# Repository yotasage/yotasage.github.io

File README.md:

# yotasage.github.io

My own collection of tools, so I don't have to search other people's websites for one that is good enough, without
ads and bad design.

**Site:** https://yotasage.github.io/

Every tool runs entirely in the browser. There is no server: the site is a static export hosted on GitHub Pages, and
files given to a tool never leave the device.

| | |
| :-: | :-: |
| <br>[**PCB viewer**](https://yotasage.github.io/pcb-viewer/main) — Gerber, KiCad, Altium, PADS & EAGLE | <br>[**EM simulation**](https://yotasage.github.io/em-sim/main) — 2D trace solver, 3D vias & WebGPU FDTD |
| <br>[**Smith chart**](https://yotasage.github.io/smith-chart/main) — Interactive matching, solver & TikZ export | <br>[**Resistor lookup**](https://yotasage.github.io/resistor/main) — E-series, SMD/colour codes, combinations & design |
| <br>[**3D viewer**](https://yotasage.github.io/3d-viewer/main) — STEP, IGES, BREP & mesh formats | <br>[**PDF tools**](https://yotasage.github.io/pdf/main) — 33 private client-side PDF utilities |

## Tools

Every tool has a card on the main page ([pages/index.tsx](pages/index.tsx)).

| Tool | Page | What it does |
| --- | --- | --- |
| FFT & coherent sampling | [/simsetup/main](https://yotasage.github.io/simsetup/main) | Calculates sampling parameters for FFTs and simulations (f0, FS, Ncyc, Npts and what follows from them), with checks for coherent sampling. |
| QR code generator | [/qrcode/main](https://yotasage.github.io/qrcode/main) | QR Code Model 1 and 2, Micro QR and rMQR with control over every parameter. Exports PNG, JPG, SVG and PDF. |
| QR code reader | [/qr-reader/main](https://yotasage.github.io/qr-reader/main) | Reads QR Code, Micro QR and rMQR (and, when asked, Data Matrix, Aztec, PDF417, EAN, UPC, Code 128 and other barcodes) from the camera (pausing at the first code or adding each new one; camera choice, light and zoom where the phone has them), from images, screenshots and every page of a PDF (chosen, dropped or pasted), several codes per picture, also inverted, mirrored or turned, with each code outlined and numbered; a code that is found but too damaged is outlined and said so. Shows what a code holds: Wi-Fi networks (password hidden until shown), eSIM activation codes (SM-DP+ address and activation code to copy, and Apple's install link on an iPhone), links with warnings for look-alike addresses, user names before "@", plain http and link shorteners, contacts (vCard, MeCard, BIZCARD; saved as .vcf), calendar events (.ics), email, SMS, phone numbers, locations with map links, two-factor accounts with their live codes (otpauth and Google Authenticator's export), SEPA (EPC) and Swiss QR bill payments with IBAN and reference checks, crypto payment links, GS1 product data and Digital Links, Matter setup codes with the manual pairing code, boarding passes (IATA BCBP), Wi-Fi Easy Connect, JSON, data URLs, the generator's password-protected text (decrypted with the password), and images, ZIP, gzip or zlib data stored as bytes. Joins structured-append messages from any pictures. A raw view gives the text with control and invisible characters named, a hex dump and the bytes read in another character set; a symbol view redraws the modules with version, error correction, mask and the symbology identifier. Typed or pasted text is shown the same way. |
| PDF tools | [/pdf/main](https://yotasage.github.io/pdf/main) | 33 client-side PDF tools: reading, visual and text comparison, merging, splitting, organizing, rotating, removing and extracting pages, compressing, web optimization (linearizing), repairing, self-hosted OCR, editing, signing, filling forms, page numbers, watermarks, cropping, resizing, N-up, grayscale, dark mode/invert, redacting, protecting, unlocking, converting to/from images and PDF/A, flattening, and editing or removing metadata, with in-memory handoff between tools. Plan: [docs/pdf-tools-plan.md](docs/pdf-tools-plan.md). |
| Base64 image converter | [/base64-image/main](https://yotasage.github.io/base64-image/main) | Image to Base64, a data URL or an HTML, CSS or Markdown snippet (optionally converted to PNG, JPEG or WebP first), and Base64 back to an image to view, download or copy. |
| Text case converter | [/text-case/main](https://yotasage.github.io/text-case/main) | Sentence case, lower case, UPPER CASE, Capitalized Case, Title Case (Chicago or APA), alternating and inverse case, and names for code (camelCase, PascalCase, snake_case, CONSTANT_CASE, kebab-case, Train-Case, dot.case), with character, word and line counts. |
| 3D viewer | [/3d-viewer/main](https://yotasage.github.io/3d-viewer/main) | Views STEP, IGES and BREP (with Open CASCADE), STL, 3MF, AMF, OBJ, PLY, OFF, VTK, glTF/GLB, FBX, Collada, KMZ, 3DS, USD/USDZ, VRML, XYZ, PCD, G-code and MagicaVoxel files. Several files can be opened together and moved apart to compare them. Section view, distance measuring, size, surface area and volume, a parts tree, and saving as STL, OBJ, PLY, GLB or PNG. |
| PCB viewer | [/pcb-viewer/main](https://yotasage.github.io/pcb-viewer/main) | Views the Gerber and drill files of a circuit board (Gerber RS-274X and X2, also the old commands of older files; Excellon with slots and routed holes, also without a header, whose format is then found from the pads; Gerber drill files) or a KiCad board (.kicad_pcb of KiCad 4 to 10, and footprints, .kicad_mod), an Altium board (.PcbDoc, binary and ASCII, and binary footprint libraries, .PcbLib), a PADS ASCII board (.asc of PowerPCB V4.0 to current PADS Layout; a binary .pcb is to be exported as ASCII in PADS) or an EAGLE board (.brd of EAGLE 6 to 9 and the EAGLE files Fusion 360 exports, and libraries, .lbr; a binary .brd from before EAGLE 6 is to be saved as XML), opened as files, a folder or ZIP archives. A pick-and-place file opened with Gerber files (KiCad's CSV and .pos, Altium's, JLCPCB's, EAGLE's .mnt and .mnb, Fusion 360's, or any table whose columns are chosen by hand; recognised by content) marks each part on the board with its rotation and designator, top and bottom, and lists the parts; its units, origin and negated bottom X are fitted to the pads when the file does not say, and can be changed. A KiCad board is drawn as KiCad plots it: pads of every shape with their solder mask and paste openings, tracks, vias, zones as last filled, graphics, text in KiCad's stroke font (or the outlines the file stores for TrueType text) and holes; from a project folder the board file is chosen and copies in backups are left out. An Altium board is drawn with its layer stack and mechanical layers, pad stacks, solder mask and paste openings from the pads and the design rules, vias, tracks, fills, regions, polygons as last poured, internal planes (with clearances and thermal reliefs), board cutouts, and text in the stroke font in the place and size of Altium's own. A PADS board is drawn with its layers from the file's layer data, part decals (outlines, copper of pins, labels), pad stacks (round, square, rounded, annular, oval and rectangular fingers with offsets, drills, slots, plating, solder mask and paste entries), routes with arcs, vias and teardrops, copper pours as last flooded, 2D lines, keep-outs and copper cut-outs, the board outline with its cutouts, and text in the stroke font in the place and size of PADS's own; plane areas whose flood the file does not keep are drawn from their outlines, clear of other nets by the design rules, and CAM planes as negative planes with antipads and thermal reliefs. An EAGLE board is drawn with its layer setup and layers, the packages of its elements placed and mirrored for the bottom, pads and vias sized by the design rules (restring, octagon, long and offset pads, SMD roundness, solder stop and cream masks), wires with arcs, holes, plain items, smashed attribute texts, and text in the stroke font in the place and size of EAGLE's vector font; EAGLE stores no copper for its polygons, so they are drawn from their outlines, clear of other signals by their isolation and the design rules, by rank, without thermal reliefs or the removal of islands. The layers are identified from their X2 attributes, the Gerber job file or their file names (KiCad, Altium, EAGLE, OrCAD, DipTrace, EasyEDA, PADS), and each can be shown, hidden, recoloured, made transparent, reordered or given another type. A realistic view shows the top or the bottom as the board looks (board shape with cutouts, solder mask, finish, silkscreen and holes; colours from the job file, the KiCad stackup or chosen). Pan, zoom and pinch, coordinates in mm or inch, measuring in mm and mil that snaps to pads, holes and line ends, the board size, stackup, components and nets, and saving the view as PNG (on screen or the whole board at a chosen resolution, transparent if wanted) or SVG (vectors at 1:1). The shown layers can be saved as a PDF at exactly 1:1 (all on one page or one page per layer; A4, A3, Letter or a page fitted to the board; seen from the top, the bottom or each layer from its own side; in the layer colours, as on screen or black; with a title, a scale bar and the layers as PDF layers) and as DXF (in mm, each layer on a layer of its own), or the board outline and its holes as DXF for mechanical CAD; layers with clear areas (negative planes, EAGLE polygons, Gerber clear polarity) are flattened with polygon booleans, so both stay vectors. A click or tap says what is there (pad, track, via, zone, hole or component, with its net, component, pin, size, layers and drill; for Gerber files from their X2 attributes, else layer, aperture and size), and clicking again steps through what overlaps there. A net or a component can be highlighted on every layer, also in the realistic view and the saved images, from a click or from searchable lists of components and nets that zoom to it. A KiCad, Altium, PADS or EAGLE board's BOM and pick-and-place file can be saved as CSV, as KiCad writes position files, from the file's origin, the drill/place (KiCad) or board (Altium) origin or the board's corner. An Altium, PADS or EAGLE board can be saved as a KiCad board (.kicad_pcb in KiCad 9's format, which KiCad 9 and 10 open), after a warning that the conversion may be incomplete or wrong and must be checked in KiCad: the layers with their names (mechanical and other layers as user layers), nets, a footprint per component with its pads (every shape, pad stacks, holes and slots, solder mask and paste margins), graphics, texts, reference and value, tracks, arcs and vias (blind, buried and micro too), zones with their saved fill, keep-outs and cut-outs as rule areas, and the board outline; planes whose copper the file does not keep (internal and CAM planes, PADS plane areas, EAGLE polygons) are zones filled with the copper drawn here. Other files are listed with what they are. Plan: [docs/pcb-viewer/plan.md](docs/pcb-viewer/plan.md). |
| Smith chart | [/smith-chart/main](https://yotasage.github.io/smith-chart/main) | Builds a matching circuit from the load to the source out of series and shunt R, L and C, transmission lines, open and short stubs and λ/4 transformers (up to 24 parts; Z0, f0 and the load typed, ideal parts and lossless lines), and draws its path on a Smith chart: every part's exact arc in its colour with an arrow in the direction of travel, a marker at every node and the match with a VSWR 1.5 circle. The grid shows impedance, admittance or both and zooms and pans by mouse, keys and touch, with labels that follow the zoom; a readout gives z, y, Γ, VSWR and return loss under the pointer. Parts are added, removed and reordered by mouse or keys, their values typed in any of their forms (R, L or C, the reactance or susceptance at f0, the normalised value, a line's length in λ or degrees and its Zc), dragged by a handle on the chart (snapping to the grid circles and to standard values: E6–E96, an own pasted list or any value per kind; Alt or the Snap switch off), stepped by arrow keys, or drawn out of the input with the draw tool; a node table gives z, Γ, VSWR and return loss of every node. Finds missing values: mark one or two values (or f0, or a line's Zc) as unknown and pick a goal at any node (the centre, a point Z, a VSWR, |Γ| or return-loss circle or limit, an r, g, x or b circle), and it lists every solution with |Γ|, the construction's two circles on the chart, a preview path and Apply, the nearest standard values and what they cost in match, the ranges that keep an inequality goal, families of two unknowns with a slider, and plainly why there is none; with nothing marked it suggests the smallest change of one or two values that meets the goal. A frequency sweep draws Γ(f) on the chart with markers, a return-loss or VSWR plot and the band figures, and a report prints it all. Exports, made on the device: the chart as a figure for a report (a TikZ picture or standalone document, SVG, PNG at 1× to 8×; column, text or page width or any width, detail presets or each item on its own, colour, greyscale or black and white, previewed at true size), CSV of the nodes, the trace and the markers, Touchstone `.s1p` of S11 over the sweep, and the project file (circuit, goal, sweep, value lists and export settings; opened again by a file picker or a drop on the page), and Copy link. An Equations panel shows the equations of any part, node or readout with your numbers, coloured and linked both ways to the chart, with step-by-step derivations, and "Explain this move" says in words what a part does to the path. A Theory section explains the chart, the solver and the sweep with live numbers, equations and citations, and every control has a short line linking to it. Learn: 16 worked examples with a guide that checks each step, exercises of five kinds with a hint ladder, and lesson links that lock parts of the page for a student. Undo and redo (200 steps), Start over, light and dark themes, every task by keyboard alone and by touch, checked in Edge, Firefox and WebKit, and the whole circuit is in the link. How to use it: [docs/smith-chart/howto.md](docs/smith-chart/howto.md); plan: [docs/smith-chart/plan.md](docs/smith-chart/plan.md). |
| Resistor lookup | [/resistor/main](https://yotasage.github.io/resistor/main) | Reads a resistance in any notation (4k7, 4,7 kΩ, 4700, 10m), the marking of a chip resistor (three or four characters, EIA-96, milliohm forms, also upside down) or the colours of 3 to 6 bands from either end, shows every reading when a text has several (digits alone are a value first, or a marking first when "Read as" says so; a reading from the other end is marked more likely or unlikely), and gives the value below, above and nearest in E3 to E192 with signed errors, the colour bands and the SMD markings. Draws the part as an axial resistor with 3 to 6 bands (four body sizes and colours) or as a chip resistor of any size from 01005 to 2512 with its marking (3 digits, 4 digits or EIA-96), in a realistic and a flat style: click a band to choose its colour, read the part from the other end, or type the marking, and the value follows. Saves the drawing as SVG, PNG, JPG or WebP at a chosen width and background, with a caption and scale bar or as the part alone, or copies it; the flat drawing is also saved or copied as TikZ for LaTeX (a `.tex` file that compiles as it is). Combinations finds the networks of 1 to 4 real resistors (series, parallel or both) that come closest to the value, from an E-series over a range or from your own value lists (pasted in any notation, kept in the browser, carried by the link): a small circuit drawing, the formula, the signed error, worst-case and RSS tolerance for each, the share of voltage, current and power in every resistor, watts and the smallest chip size for a voltage or a current, copy as text and save as CSV. Design finds the resistors for a circuit and checks them over tolerance and temperature: a single resistance for a current or a voltage (with a series drop for an LED), a voltage divider with an optional load, the feedback of a regulator, a non-inverting or inverting gain, and a current-sense shunt, each with a schematic; for a target, an allowed deviation, a kind of part (tolerance and TCR), a set of temperatures (−40, 25, 85 and 125 °C unless changed) and parts that drift on their own or track, it answers in one sentence which values stay inside, or which tolerance and TCR would be needed, and lists the candidates (also two values in series or parallel) with the worst case and RSS at each temperature in a range chart, and the voltage, current and power in each resistor against the derated rating of a chip size. Reference tables (colour code, SMD markings, EIA-96, chip and axial sizes with limiting voltages) mark the current value and use what is clicked; where makers disagree the page says so (an EIA-96 marking with R or S is read both ways). Theory explains what stands behind the numbers in fourteen short topics that fold (Ohm's law and power, series, parallel and dividers, the E-series, reading the codes, technologies compared, tolerance and temperature with worst case and RSS, power, derating and limiting voltage, pulses, noise, voltage coefficient, high frequency, ageing, zero-ohm links, current sensing), with formulas, small figures and live numbers for the current value (current and power at a typed voltage, thermal noise, the derating curve of the chosen chip size, the series the value is in). Every sourced statement is cited, and References lists the sources (datasheets, application notes, the standards and the original papers) from `references.bib`, numbered by first citation. Light and dark themes, and every result is a link. How it was built is in [docs/resistor/plan.md](docs/resistor/plan.md). |
| EM simulation | [/em-sim/main](https://yotasage.github.io/em-sim/main) | Works out the impedance of PCB traces and vias with field solvers, on a stackup you type, any of JLCPCB's stackups or the stackup and net classes of a KiCad board. Traces (a 2D field solver): Z0, Zdiff, Zcm, Zodd, Zeven, εeff, delay, crosstalk, L and C, each with the solver's error, for microstrip, stripline, coplanar lines with or without ground, edge- and broadside-coupled pairs or any arrangement of traces and planes; sizes dragged in the drawing, the fields of the cross-section drawn, the width for a target, sweeps, worst case, Monte Carlo and a ranking of the tolerances, and a comparison with closed-form calculators and the inputs JLCPCB's calculator uses. Vias and via pairs (pads, antipads, return vias, backdrill, feeds): drawn from the side, from above and in 3D with their fields, the impedance of the barrel and the whole via, the pads' capacitance, stub resonance, TDR, TDT and S-parameters (mixed-mode for a pair), and the antipad or return-via distance for a target. Full-wave (FDTD) runs of a via or a trace section on the GPU with WebGPU or on the CPU, with their TDR and S-parameters beside the quasi-static ones and their waves played on a slice and on cut planes in 3D. A Theory section with live numbers, equations with step-by-step derivations, citations and five worked examples; every control has a short line linking to it. Exports made on the device: figures as TikZ, SVG and PNG, CSV, Touchstone, a project file and a printable report. Checked against exact solutions, a separate finite-difference solver, JLCPCB's calculator and openEMS, and in Edge, Firefox and WebKit by keyboard and touch. How to use it: [docs/em-sim/howto.md](docs/em-sim/howto.md); plan: [docs/em-sim/plan.md](docs/em-sim/plan.md). |

The [/licenses](https://yotasage.github.io/licenses) page, linked from the footer of every page, lists the licences
of the packages the site uses.

## Getting started

Needs Node 22 or newer (GitHub builds with Node 22).

```
npm install      # also copies pdf.js, 3D viewer, QR and font assets, generates the licence list and writes sitemap.xml
npm run dev      # http://localhost:3020, also reachable from a phone on the same network
npm run build    # run before pushing; GitHub runs the same build
```

What these commands do, NVM for Windows and keeping packages up to date: [docs/npm-and-node.md](docs/npm-and-node.md).

## Deployment

Pushing to `main` runs [.github/workflows/nextjs.yml](.github/workflows/nextjs.yml), which builds the site as static
files and publishes them to GitHub Pages. The workflow adds the `output: 'export'` setting itself; the repo has no
`next.config` file. If the build fails, nothing is deployed and the previous version stays online.

## Adding a tool

1. Add the page as `pages/<tool>/main.tsx`, with a link back to the main page (`components/icons/home.tsx`).
2. Add a card for it to the `TOOLS` list in [pages/index.tsx](pages/index.tsx), with an icon in
   [components/Home/ToolIcon.tsx](components/Home/ToolIcon.tsx).
3. Keep the logic in `lib/<tool>/`, components in `components/<Tool>/` and styles in `styles/<Tool>.module.css`.
   Every file under `pages/` becomes a page on the site, so nothing else goes there.
4. Only use what works without a server: no API routes, no `getServerSideProps`, and no libraries, fonts or files
   loaded from a CDN. `getStaticProps` is fine, since it runs when the site is built.
5. Check the licence of any new package (MIT, BSD, Apache-2.0 and ISC are fine; GPL, LGPL and AGPL need a decision
   first).

## Project layout

| Folder | Contents |
| --- | --- |
| `pages/` | One file per page (Next.js Pages Router). `_app.tsx` adds the footer to every page. |
| `components/` | React components, one folder per tool. |
| `lib/` | Logic without React, one folder per tool. `bibtex.ts` and `references.ts` read [references.bib](references.bib). |
| `styles/` | CSS modules, one per tool. |
| `scripts/` | Scripts that run on `npm install`. `scripts/harness/` holds test harnesses with packages of their own, which the site does not use. |
| `public/` | Files served as they are (favicon, `robots.txt`, `public/og/` social previews, `public/samples/` built-in demo files for the PCB and 3D viewers). `public/pdfjs/`, `public/3d/`, `public/qr/`, `public/fonts/` and `public/sitemap.xml` are copied or generated on `npm install`. |
| `docs/` | Notes and plans. |

Sources cited on the site are in [references.bib](references.bib); the comment at the top of the file explains how
to cite them from a page.

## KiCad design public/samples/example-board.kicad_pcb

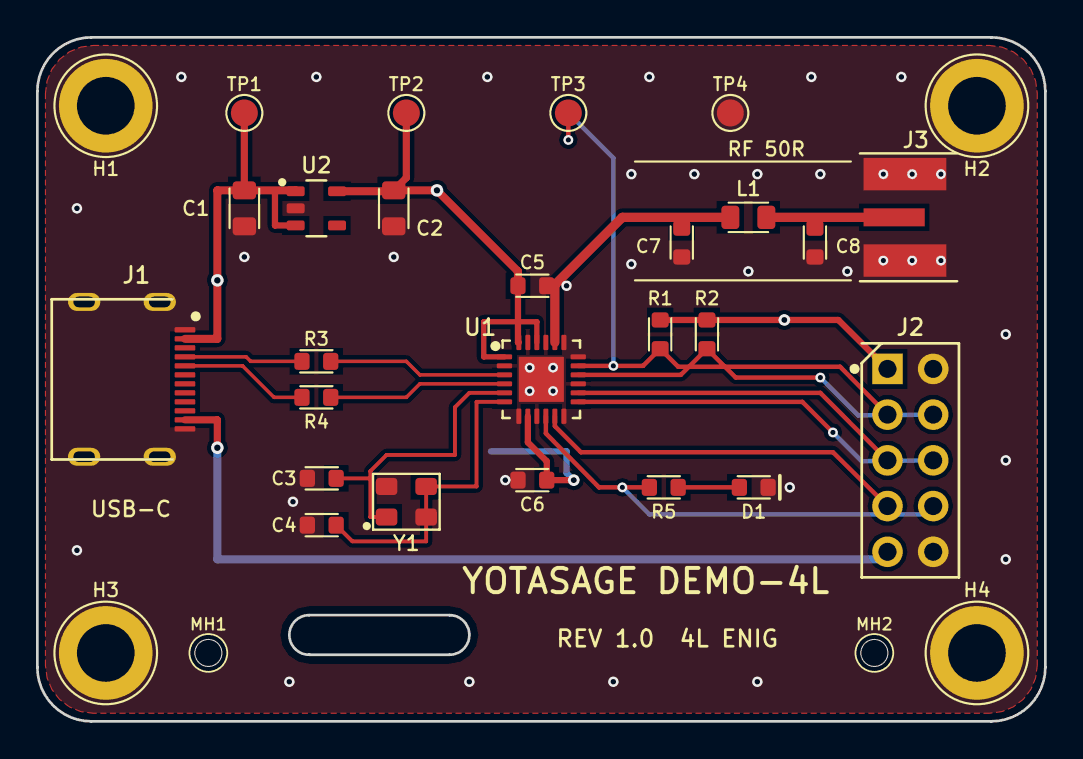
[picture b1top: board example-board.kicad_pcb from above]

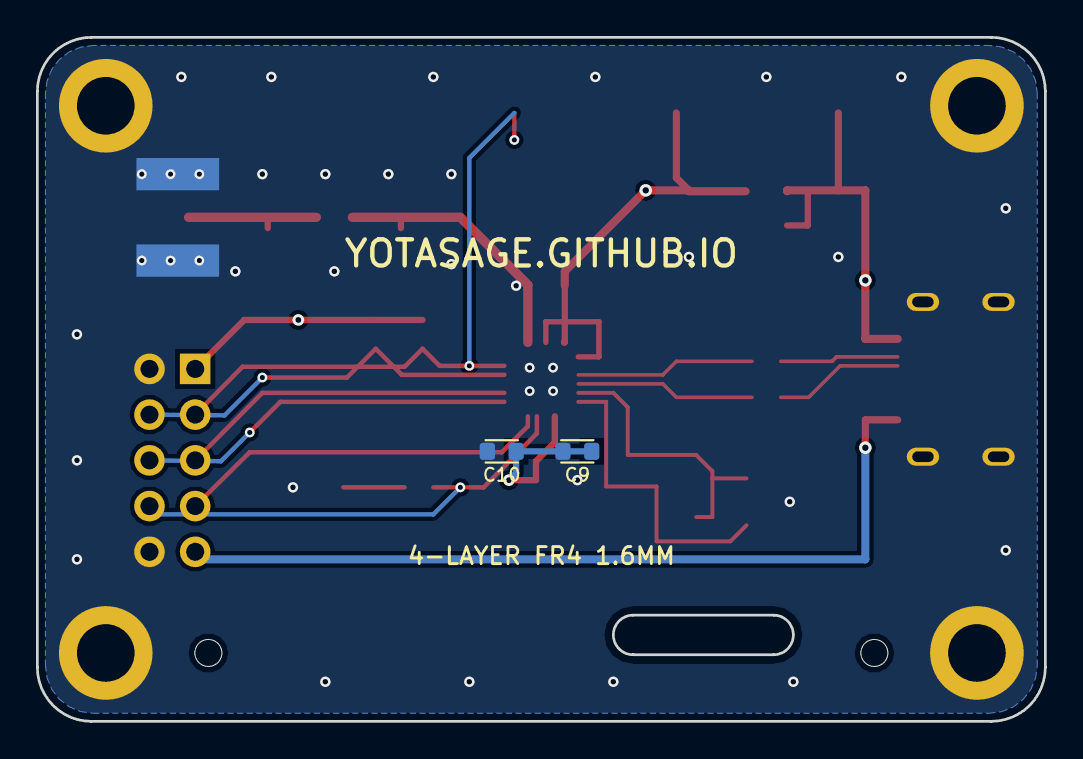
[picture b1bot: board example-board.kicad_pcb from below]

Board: 4 copper layers, 56.0 x 38.0 mm, 33 parts (2 on the bottom side), 16 nets.

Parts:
C1, C2: 10uF; C_0805_2012Metric
C3, C4: 18pF; C_0603_1608Metric
C5, C6, C9: 100nF; C_0603_1608Metric
C7, C8: 2.2pF; C_0603_1608Metric
C10: 1uF; C_0603_1608Metric
D1: GREEN; LED_0603_1608Metric
H1, H2, H3, H4: M3; MountingHole_3.2mm_M3_Pad_Via
J1: USB-C; USB_C_Receptacle_12P
J2: IO_HDR_2x5; PinHeader_2x05_P2.54mm_Vertical
J3: SMA-50R; SMA_EdgeMount_50Ohm
L1: 6.8nH; L_0805_2012Metric
MH1, MH2: Tooling; MountingHole_1.5mm_NPTH
R1, R2: 4.7k; R_0603_1608Metric
R3, R4: 22R; R_0603_1608Metric
R5: 1k; R_0603_1608Metric
TP1: +5V; TestPoint_Pad_D1.5mm
TP2: +3V3; TestPoint_Pad_D1.5mm
TP3: SDA; TestPoint_Pad_D1.5mm
TP4: GND; TestPoint_Pad_D1.5mm
U1: RF-MCU24; QFN-24-1EP_4x4mm_P0.5mm_EP2.5x2.5mm
U2: LDO-3V3; SOT-23-5
Y1: 24MHz; Crystal_SMD_3225-4Pin_3.2x2.5mm

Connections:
+3V3: C2.2, C5.1, C6.2, C9.1, C10.1, J2.1, R1.2, R2.2, TP2.1, U1.1, U1.8, U1.22, U1.24, U2.5
+5V: C1.2, J1.A4, J1.B4, J2.9, TP1.1, U2.1, U2.3
GND: C1.1, C2.1, C3.1, C4.1, C5.2, C6.1, C7.1, C8.1, C9.2, C10.2, D1.2, H1.1, H2.1, H3.1, H4.1, J1.A1, J1.B1, J1.S1, J1.S2, J1.S3, J1.S4, J2.2, J2.10, J3.2, TP4.1, U1.2, U1.7, U1.9, U1.12, U1.15, U1.18, U1.19, U1.21, U1.23, U1.25, U2.2, Y1.2, Y1.4
LED_A: D1.1, R5.2
LED_DRV: J2.8, R5.1, U1.10
RF_FILT: C7.2, L1.1, U1.20
RF_IN: C8.2, J3.1, L1.2
SCL: J2.4, R2.1, U1.16
SDA: J2.3, R1.1, TP3.1, U1.17
SIG_N: J1.A7, J1.B7, R4.1, R4.2, U1.4
SIG_P: J1.A6, J1.B6, R3.1, R3.2, U1.3
SPI_CS: J2.7, U1.11
SPI_MOSI: J2.6, U1.13
SPI_SCK: J2.5, U1.14
XTAL_IN: C3.2, U1.5, Y1.1
XTAL_OUT: C4.2, U1.6, Y1.3
